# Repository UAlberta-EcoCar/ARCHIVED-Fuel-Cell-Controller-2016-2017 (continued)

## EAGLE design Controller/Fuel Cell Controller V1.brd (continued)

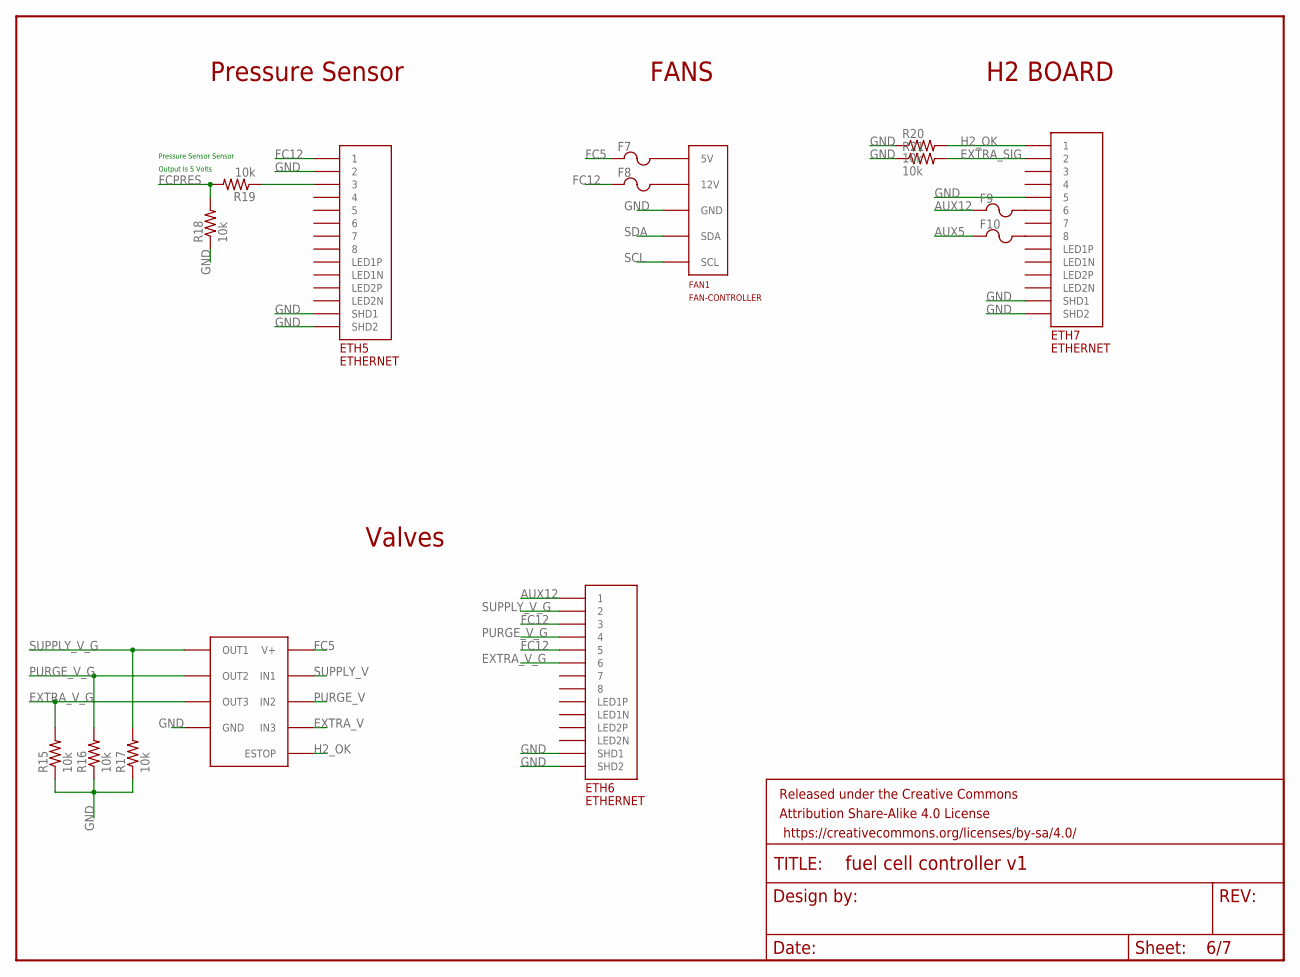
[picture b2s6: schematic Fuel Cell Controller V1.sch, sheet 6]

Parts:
ETH5, ETH6, ETH7: ETHERNET; A122645-ND
F7, F8, F9, F10: POLYFUSE; 1206
FAN1: FAN-CONTROLLER
FRAME6: FRAME-LETTERNO_PACKAGE; DUMMY
M1: MOSFETBOARD; MOSFET-BOARD
R15, R16, R17, R18, R19: 10k; 0805
R20, R21: 10k; R0603

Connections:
AUX5: F10.1; also elsewhere on the board
AUX12: ETH6.P$1 (1), F9.1; also elsewhere on the board
EXTRA_SIG: ETH7.P$2 (2), R21.2; also elsewhere on the board
EXTRA_V: M1.IN3; also elsewhere on the board
EXTRA_V_G: ETH6.P$6 (6), M1.OUT3, R15.2
FC5: F7.1, M1.VDD (V+); also elsewhere on the board
FC12: ETH5.P$1 (1), ETH6.P$3 (3), ETH6.P$5 (5), F8.1; also elsewhere on the board
FCPRES: R18.2, R19.2; also elsewhere on the board
GND: ETH5.P$2 (2), ETH5.P$13 (SHD1), ETH5.P$14 (SHD2), ETH6.P$13 (SHD1), ETH6.P$14 (SHD2), ETH7.P$5 (5), ETH7.P$13 (SHD1), ETH7.P$14 (SHD2), FAN1.GND, FAN1.GND2 (GND), FAN1.GND3 (GND), M1.GND, M1.GND1 (GND), M1.GND2 (GND), M1.VSS (GND), R15.1, R16.1, R17.1, R18.1, R20.1, R21.1; also elsewhere on the board
H2_OK: ETH7.P$1 (1), M1.ESTOP, R20.2; also elsewhere on the board
unnamed: ETH7.P$6 (6), F9.2
unnamed: ETH7.P$8 (8), F10.2
unnamed: F7.2, FAN1.5 (5V), FAN1.5_2 (5V)
unnamed: F8.2, FAN1.12 (12V), FAN1.12_2 (12V), FAN1.12_3 (12V)
unnamed: ETH5.P$3 (3), R19.1
PURGE_V: M1.IN2; also elsewhere on the board
PURGE_V_G: ETH6.P$4 (4), M1.OUT2, R16.2
SCL: FAN1.SCL; also elsewhere on the board
SDA: FAN1.SDA; also elsewhere on the board
SUPPLY_V: M1.IN1; also elsewhere on the board
SUPPLY_V_G: ETH6.P$2 (2), M1.OUT1, R17.2

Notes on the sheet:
Valves
Pressure Sensor
FANS
H2 BOARD
Pressure Sensor Sensor
Output Is 5 Volts

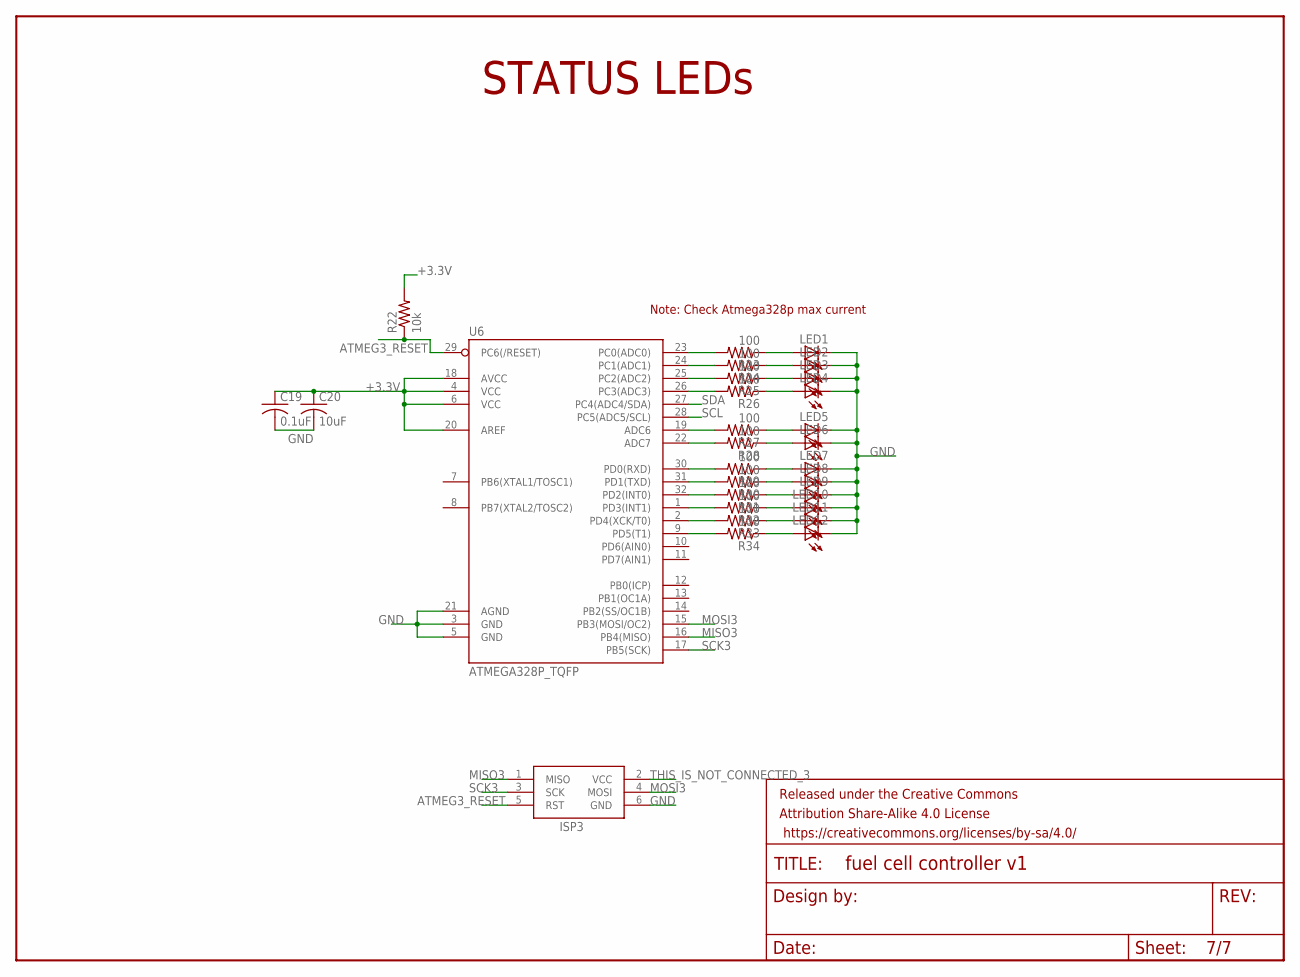
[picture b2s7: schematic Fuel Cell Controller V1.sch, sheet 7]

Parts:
C19: 0.1uF; C0603
C20: 10uF; C0603
FRAME7: FRAME-LETTERNO_PACKAGE; DUMMY
ISP3: AVRISP-BOX
LED1, LED2, LED3, LED4, LED5, LED6, LED7, LED8, LED9, LED10, LED11, LED12: LEDCHIPLED_0805; CHIPLED_0805
R22: 10k; R0603
R23, R24, R25, R26, R27, R28, R29, R30, R31, R32, R33, R34: 100; R0603
U6: ATMEGA328P_TQFP; TQFP32-08

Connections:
+3.3V: C19.1, C20.1, R22.2, U6.4 (VCC), U6.6 (VCC), U6.18 (AVCC), U6.20 (AREF); also elsewhere on the board
ATMEG3_RESET: ISP3.5 (RST), R22.1, U6.29 (PC6(/RESET))
GND: C19.2, C20.2, ISP3.6 (GND), LED1.C, LED2.C, LED3.C, LED4.C, LED5.C, LED6.C, LED7.C, LED8.C, LED9.C, LED10.C, LED11.C, LED12.C, U6.3 (GND), U6.5 (GND), U6.21 (AGND); also elsewhere on the board
MISO3: ISP3.1 (MISO), U6.16 (PB4(MISO))
MOSI3: ISP3.4 (MOSI), U6.15 (PB3(MOSI/OC2))
unnamed: R23.2, U6.23 (PC0(ADC0))
unnamed: R24.2, U6.24 (PC1(ADC1))
unnamed: R25.2, U6.25 (PC2(ADC2))
unnamed: R26.2, U6.26 (PC3(ADC3))
unnamed: R27.2, U6.19 (ADC6)
unnamed: R28.2, U6.22 (ADC7)
unnamed: R29.2, U6.30 (PD0(RXD))
unnamed: R30.2, U6.31 (PD1(TXD))
unnamed: R31.2, U6.32 (PD2(INT0))
unnamed: R32.2, U6.1 (PD3(INT1))
unnamed: R33.2, U6.2 (PD4(XCK/T0))
unnamed: R34.2, U6.9 (PD5(T1))
unnamed: LED12.A, R34.1
unnamed: LED11.A, R33.1
unnamed: LED10.A, R32.1
unnamed: LED9.A, R31.1
unnamed: LED8.A, R30.1
unnamed: LED7.A, R29.1
unnamed: LED6.A, R28.1
unnamed: LED5.A, R27.1
unnamed: LED4.A, R26.1
unnamed: LED3.A, R25.1
unnamed: LED2.A, R24.1
unnamed: LED1.A, R23.1
SCK3: ISP3.3 (SCK), U6.17 (PB5(SCK))
SCL: U6.28 (PC5(ADC5/SCL)); also elsewhere on the board
SDA: U6.27 (PC4(ADC4/SDA)); also elsewhere on the board
THIS_IS_NOT_CONNECTED_3: ISP3.2 (VCC)

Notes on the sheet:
STATUS LEDs
Note: Check Atmega328p max current

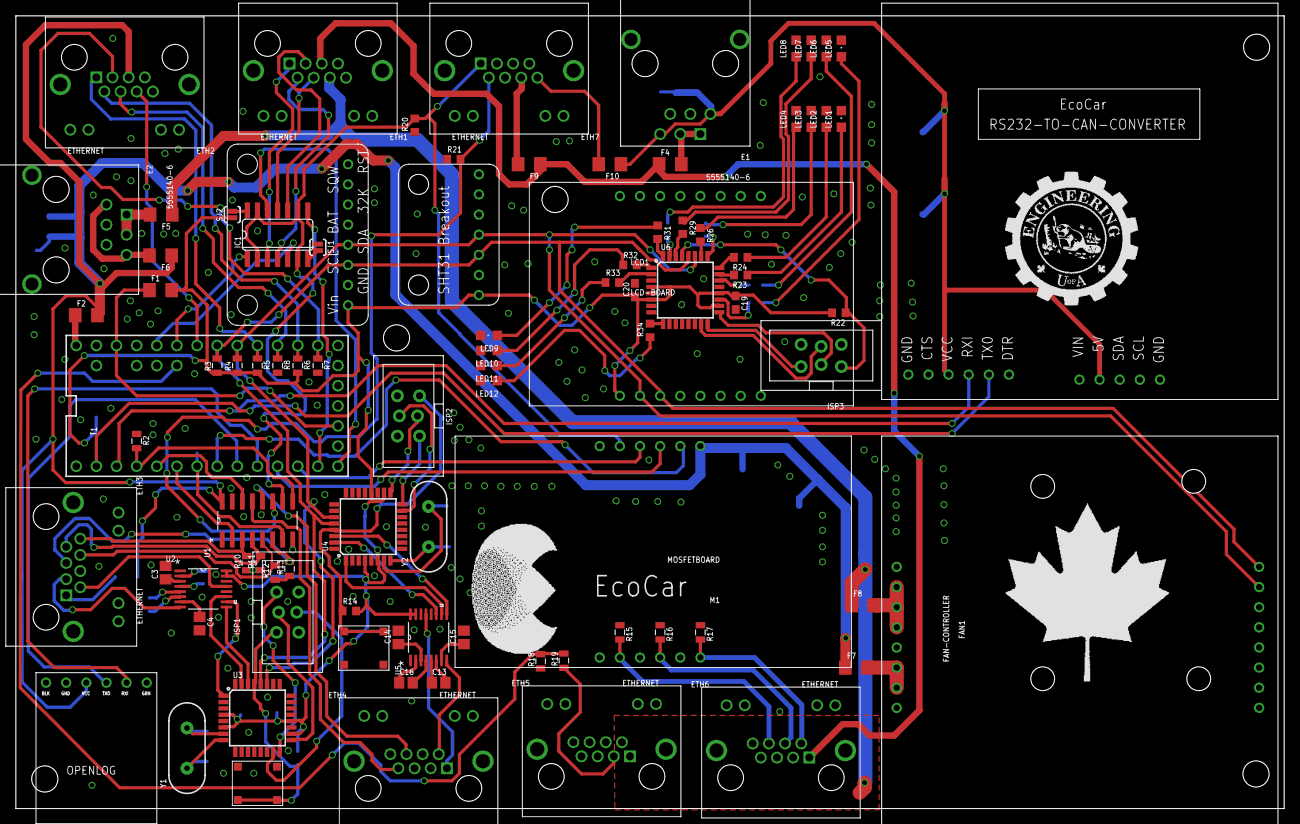
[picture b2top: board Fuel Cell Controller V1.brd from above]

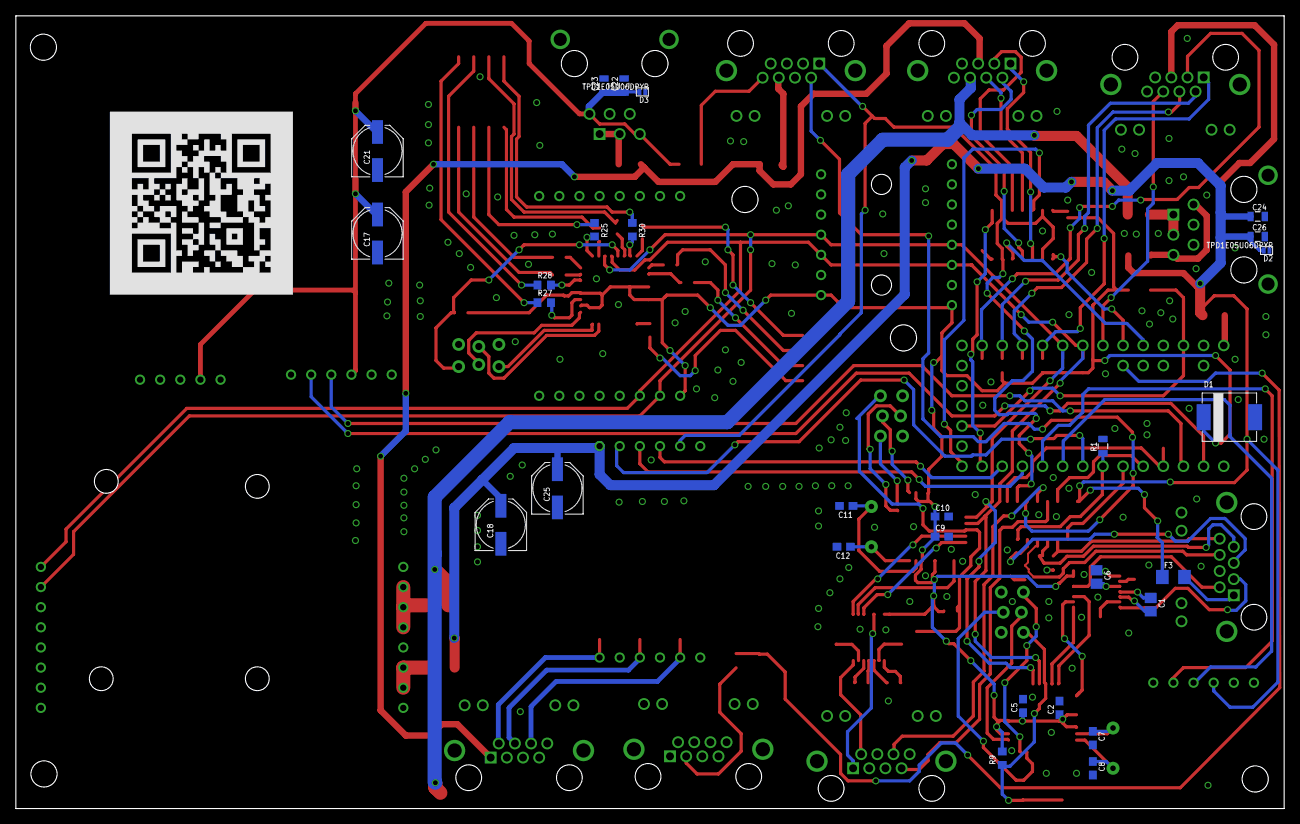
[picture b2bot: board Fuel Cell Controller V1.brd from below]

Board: 2 copper layers, 160.0 x 100.0 mm, 131 parts (29 on the bottom side), 119 nets.

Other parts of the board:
U$1: TRUMP

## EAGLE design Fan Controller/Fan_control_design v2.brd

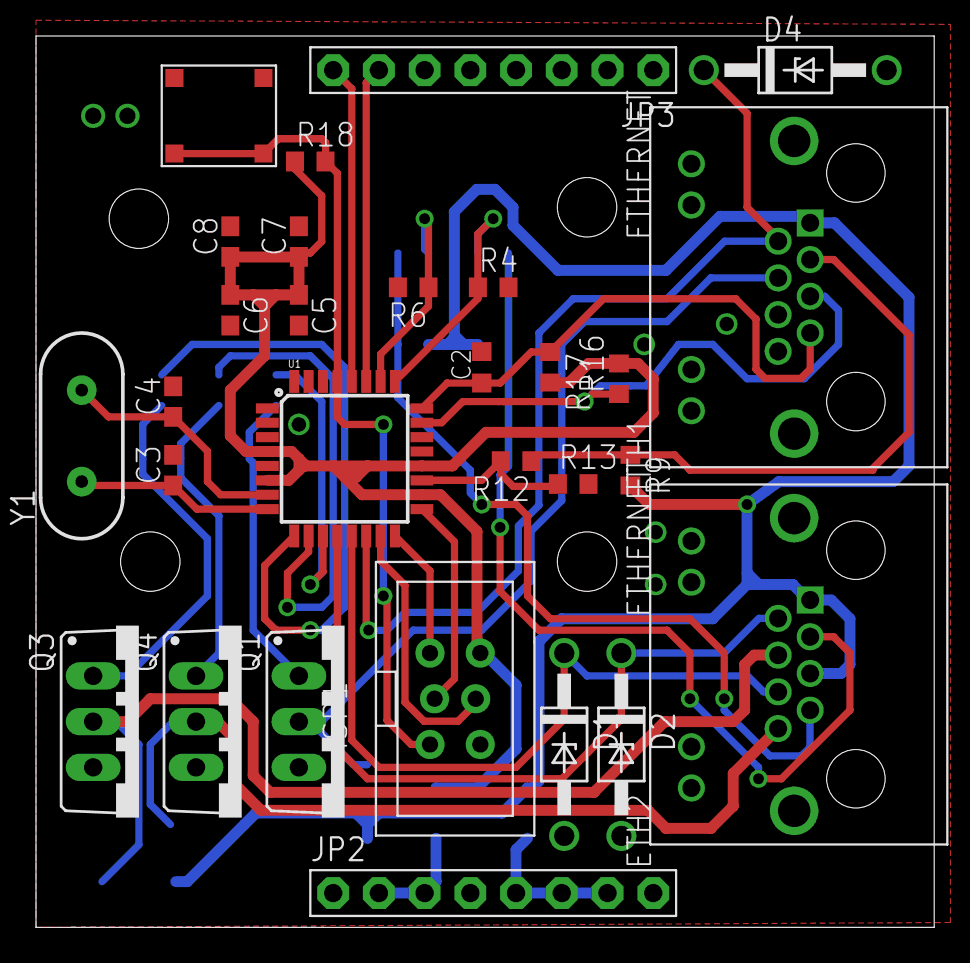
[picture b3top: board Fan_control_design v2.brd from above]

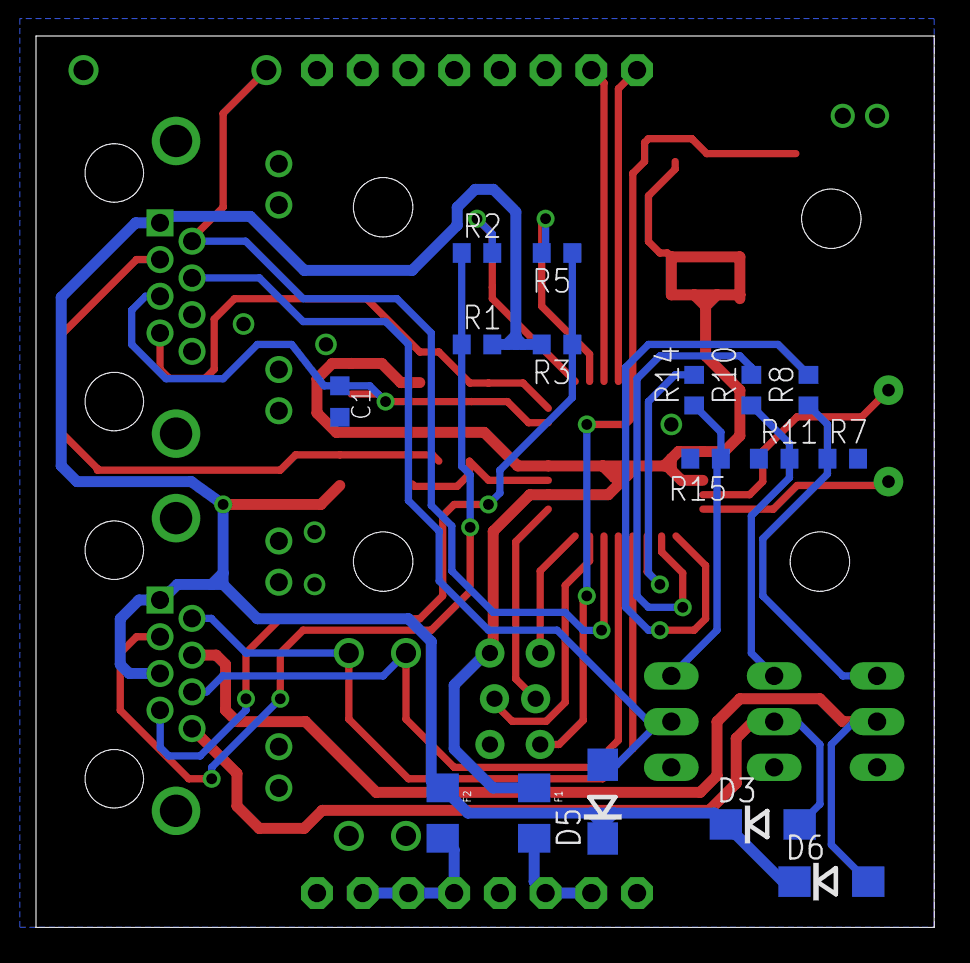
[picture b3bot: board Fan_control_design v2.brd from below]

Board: 2 copper layers, 49.9 x 49.5 mm, 49 parts (16 on the bottom side), 33 nets.

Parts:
C1, C2: C0603K
C3, C4: 22pf; C0603
C5, C6: 0.1uf; C0603
C7, C8: 10uf; C0603
D1, D2, D4: 1N4728; DO41Z10
D3, D5, D6: DO214AC
ETH1, ETH2: ETHERNET; A122645-ND
F1, F2: 1206
ISP1: AVRISP-BOX
JP2, JP3: 1X08-BIG
Q1, Q3, Q4: IRF520; TO220BV
R1, R2, R3, R5, R7, R9, R11, R12, R15, R18: 10k; R0603
R4, R6, R13: 4k7; R0603
R8, R10, R14: 250; R0603
R16, R17: 100K; R0603
STANDOFF1, STANDOFF2, STANDOFF3, STANDOFF4: STAND-OFF
U1: ATMEGA328P_TQFP; TQFP32-08
U$3: EG4621CT-ND
Y1: HC49US

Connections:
12V: D3.C, D5.C, D6.C, ETH1.P$1, ETH2.P$1, ETH2.P$5, F2.1, R1.2, R3.2, R9.2
+5V: C5.1, C6.1, C7.1, C8.1, F1.1, ISP1.2, R16.2, R17.2, R18.1, U1.4, U1.6, U1.18, U1.20
GND: C1.2, C2.2, C3.2, C4.2, C5.2, C6.2, C7.2, C8.2, D1.A, D2.A, D4.A, ETH1.P$6, ETH1.P$8, ETH1.P$13, ETH1.P$14, ETH2.P$13, ETH2.P$14, ISP1.6, JP3.4, JP3.5, JP3.6, Q1.S, Q3.S, Q4.S, R4.2, R6.2, R7.2, R11.1, R13.2, R15.1, U1.3, U1.5, U1.21, U$3.P$1, U$3.P$2
MISO: ISP1.1, U1.16
MOSI: ISP1.4, U1.15
MOS_1: R8.2, U1.9
MOS_2: R10.2, U1.10
MOS_3: R14.2, U1.11
unnamed: F1.2, JP2.2, JP2.3
unnamed: F2.2, JP2.5, JP2.6, JP2.7
unnamed: C3.1, U1.8, Y1.1
unnamed: Q3.G, R7.1, R8.1
unnamed: C4.1, U1.7, Y1.2
unnamed: Q4.G, R10.1, R11.2
unnamed: Q1.G, R14.1, R15.2
PWM_1: D2.C, ETH2.P$2, U1.12
PWM_2: D1.C, ETH2.P$6, U1.13
PWM_3: D4.C, ETH1.P$2, U1.14
PWR_1: D6.A, ETH2.P$4, Q3.D
PWR_2: D3.A, ETH2.P$8, Q4.D
PWR_3: D5.A, ETH1.P$4, Q1.D
RESET: ISP1.5, R18.2, U1.29, U$3.P$3, U$3.P$4
SCK: ISP1.3, U1.17
SCL: JP3.8, U1.28
SDA: JP3.7, U1.27
TACH_1: R2.2, R4.1, U1.25
TACH_1_IN: ETH2.P$3, R1.1, R2.1
TACH_2: R5.2, R6.1, U1.26
TACH_2_IN: ETH2.P$7, R3.1, R5.1
TACH_3: R12.2, R13.1, U1.19
TACH_3_IN: ETH1.P$3, R9.1, R12.1
THERM1: C1.1, ETH1.P$5, R16.1, U1.23
THERM2: C2.1, ETH1.P$7, R17.1, U1.24

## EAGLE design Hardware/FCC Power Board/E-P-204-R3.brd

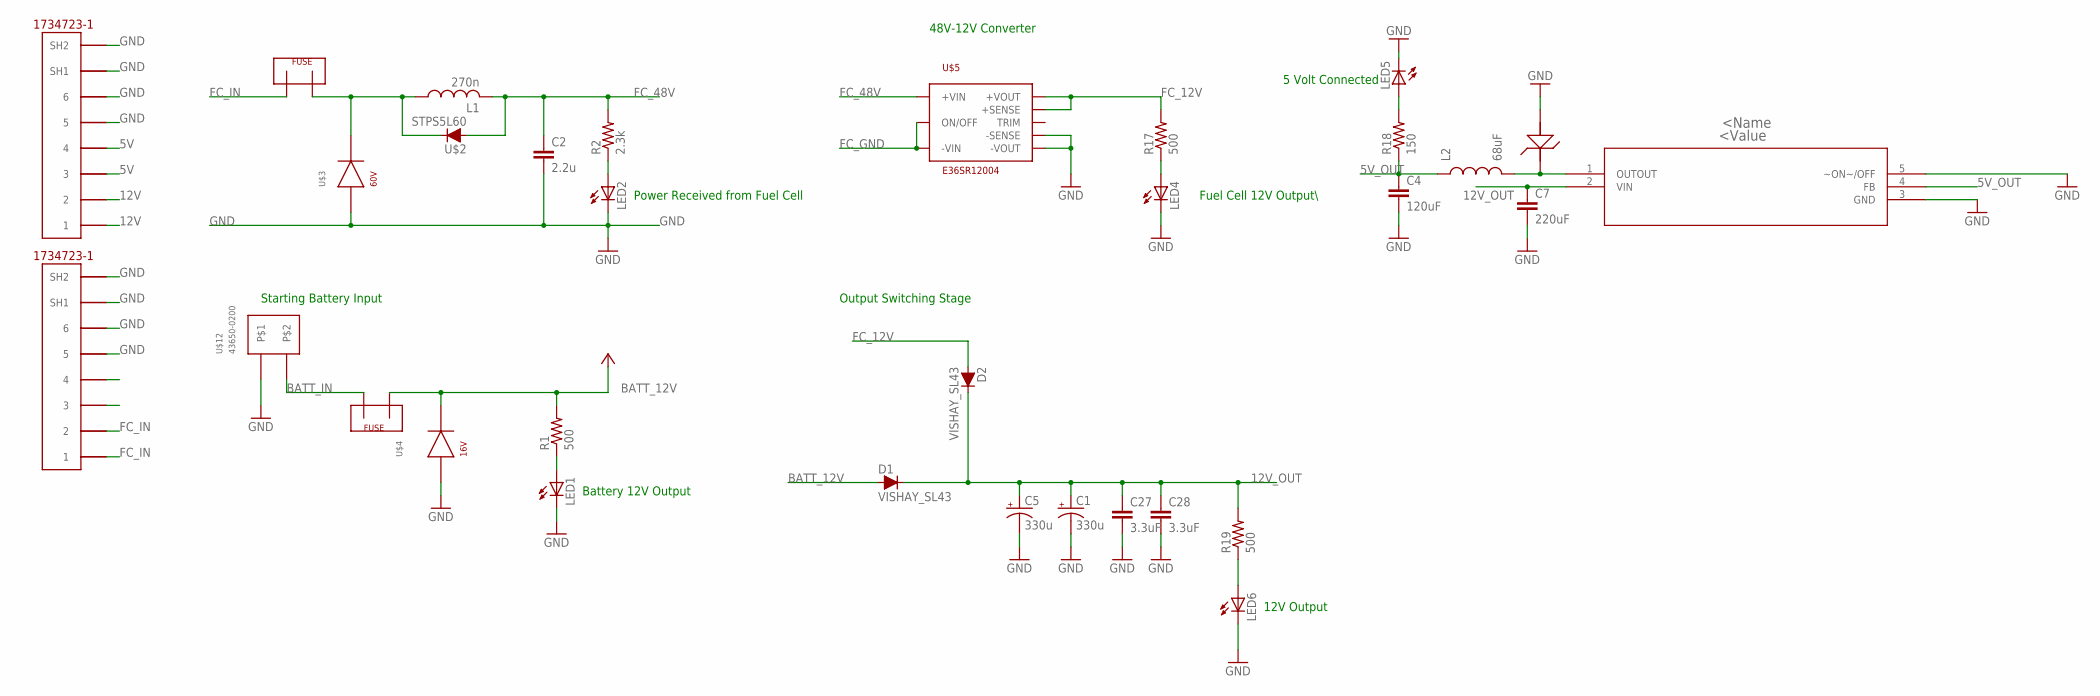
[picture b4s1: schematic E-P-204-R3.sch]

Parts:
C1, C5: 330u; PANASONIC_E
C2: 2.2u; C1210
C4: 120uF; 0805
C7: 220uF; 0805
C27, C28: 3.3uF; C0805K
D1, D2: VISHAY_SL43; DO-214AB_SMC
L1: 270n; L3225P
L2: 68uF; 0805
LED1, LED2, LED4, LED5, LED6: LED1206; LED-1206
R1, R17, R19: 500; M0805
R2: 2.3k; M0805
R18: 150; M0805
U$2: STPS5L60; STM_SMC
U$3: SMBJ60CA; .277X.089
U$4: SMAJ16CA; .25X.07
U$5: E36SR12004; 2.30X0.90X0.34
U$6, U$11: 5555140-6; 1734723-1_RJ11
U$7, U$10: FUSEMINI-BLADE; MINI-BLADE-FUSE
U$8: LM2595T-5.0; T05D
U$9: MURS120T3G
U$12: 43650-0200

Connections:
5V: U$11.3, U$11.4
5V_OUT: C4.1, L2.1, R18.1, U$8.4 (FB)
12V: U$11.1, U$11.2
12V_OUT: C1.+, C5.+, C7.1, C27.1, C28.1, D1.C, D2.C, R19.2, U$8.2 (VIN)
BATT_12V: D1.A, R1.2, U$4.CATHODE, U$10.OUT
BATT_IN: U$10.IN, U$12.P$1
FC_12V: D2.A, R17.2, U$5.P$7 (+SENSE), U$5.P$8 (+VOUT)
FC_48V: C2.1, L1.2, R2.2, U$2.A, U$5.P$1 (+VIN)
FC_FUSED: L1.1, U$2.C, U$3.CATHODE, U$7.IN
FC_GND: U$5.P$2 (ON/OFF), U$5.P$3 (-VIN)
FC_IN: U$6.1, U$6.2, U$7.OUT
GND: C1.-, C2.2, C4.2, C5.-, C7.2, C27.2, C28.2, LED1.C, LED2.C, LED4.C, LED5.C, LED6.C, U$3.ANODE, U$4.ANODE, U$5.P$4 (-VOUT), U$5.P$5 (-SENSE), U$6.5, U$6.6, U$6.SH1, U$6.SH2, U$8.3 (GND), U$8.5 (~ON~/OFF), U$9.P$2 (PIN1), U$11.5, U$11.6, U$11.SH1, U$11.SH2, U$12.P$2
unnamed: LED1.A, R1.1
unnamed: LED2.A, R2.1
unnamed: L2.2, U$8.1 (OUTOUT), U$9.P$1
unnamed: LED5.A, R18.2
unnamed: LED4.A, R17.1
unnamed: LED6.A, R19.1

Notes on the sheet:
Output Switching Stage
Starting Battery Input
48V-12V Converter
Power Received from Fuel Cell
Battery 12V Output
Fuel Cell 12V Output\
12V Output
5 Volt Connected

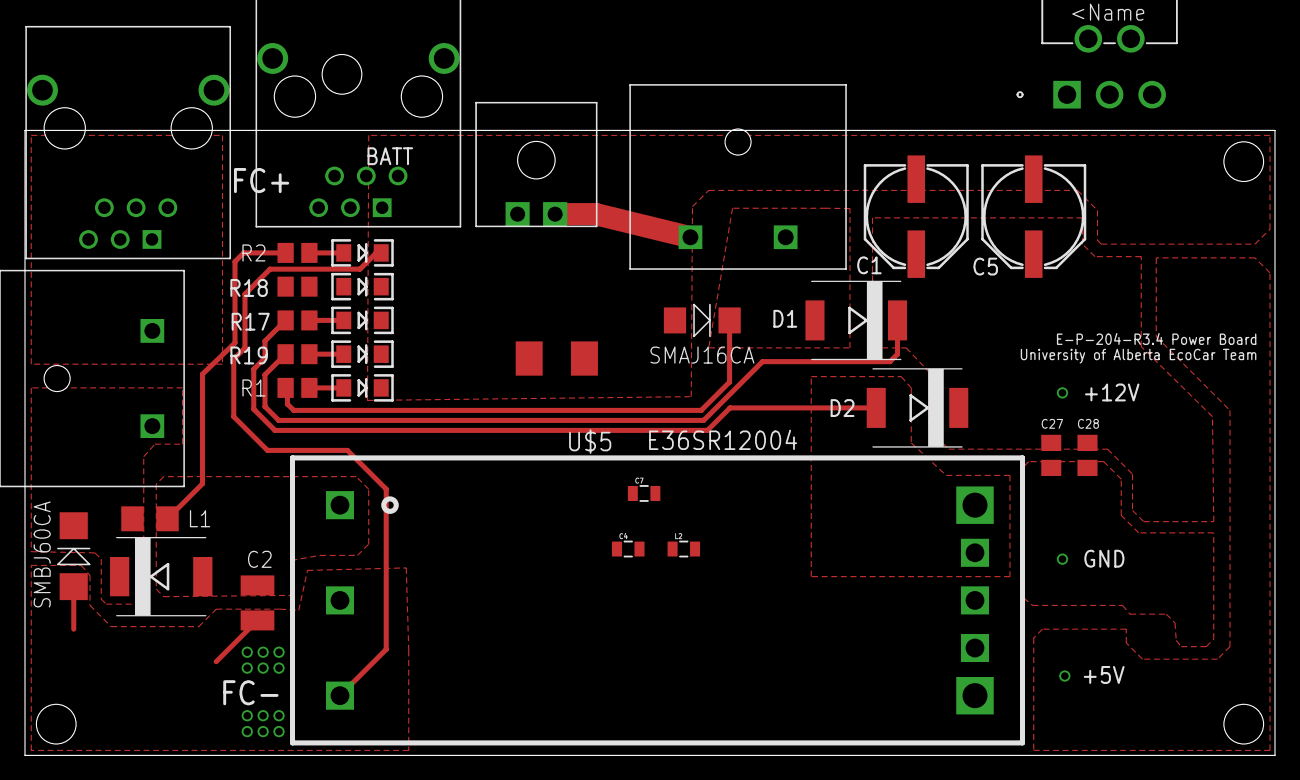
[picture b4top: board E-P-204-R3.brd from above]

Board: 2 copper layers, 100.0 x 50.0 mm, 32 parts (0 on the bottom side), 18 nets.

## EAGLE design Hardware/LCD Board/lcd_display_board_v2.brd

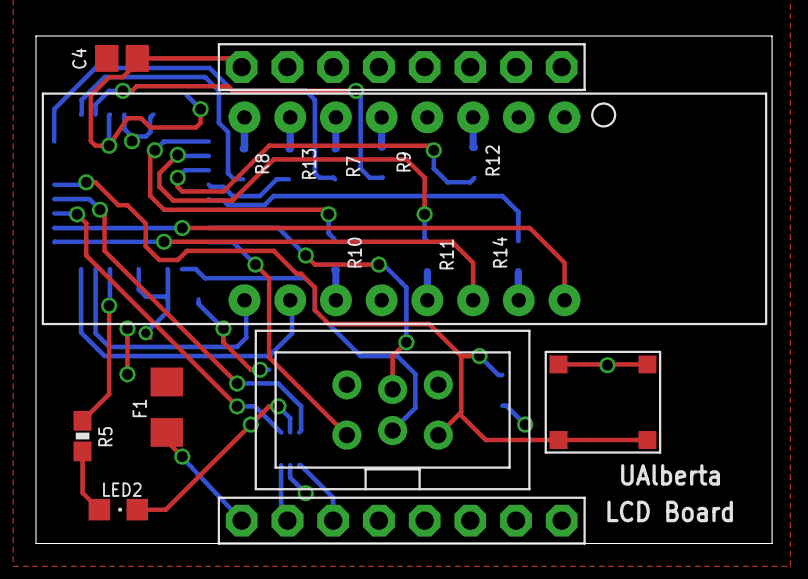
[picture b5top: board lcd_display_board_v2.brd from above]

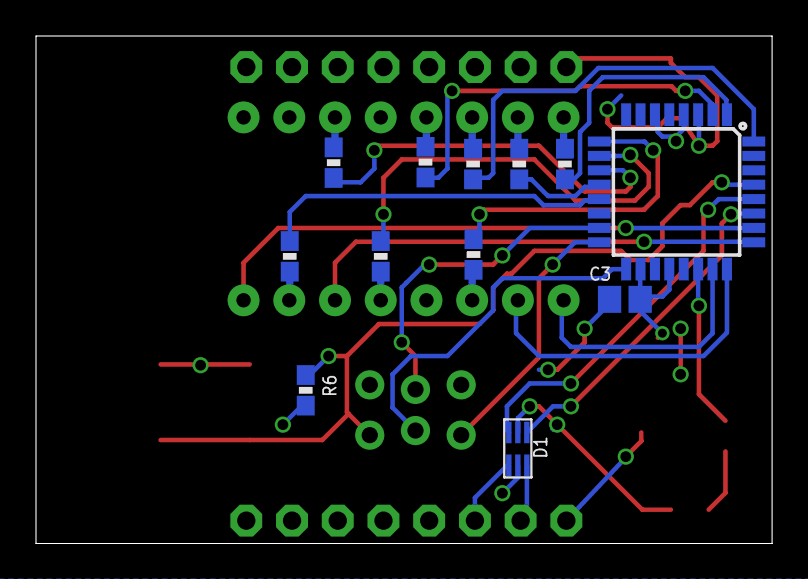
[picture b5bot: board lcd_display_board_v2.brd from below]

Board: 2 copper layers, 40.9 x 28.2 mm, 21 parts (12 on the bottom side), 33 nets.

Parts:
C3: 1uF; C0805
C4: 0.1uF; C0805
D1: USBLC6-2SC6
F1: 1206
ISP1: AVRISP-BOX
JP1, JP2: 1X08-BIG
LED1: 7-SEGMENT-4DIGIT-YOUNGSUN
LED2: CHIPLED_0805
R5: 1k; 0603-RES
R6: 10k; 0603-RES
R7, R8, R9, R10, R11, R12, R13, R14: 80 Ohm; 0603-RES
U1: ATMEGA328P_TQFP; TQFP32-08
U$10: EG4621CT-ND

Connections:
+3.3V: C3.1, C4.1, D1.P$5, F1.1, R6.2, U1.4, U1.6, U1.18, U1.20
ATM_RESET: ISP1.5, R6.1, U1.29, U$10.P$3, U$10.P$4
DIG1AN: LED1.1, U1.23
DIG2AN: LED1.2, U1.24
DIG3AN: LED1.6, U1.25
DIG4AN: LED1.8, U1.26
GND: C3.2, C4.2, D1.P$2, ISP1.6, JP1.4, JP1.5, JP1.6, JP1.7, JP1.8, JP2.1, JP2.2, JP2.3, JP2.4, JP2.5, JP2.6, JP2.7, JP2.8, LED2.C, U1.3, U1.5, U1.21, U$10.P$1, U$10.P$2
MISO: ISP1.1, U1.16
MOSI: ISP1.4, U1.15
unnamed: F1.2, JP1.1
unnamed: D1.P$6, JP1.2
unnamed: R5.1, U1.22
unnamed: LED2.A, R5.2
unnamed: R7.1, U1.32
unnamed: R8.1, U1.1
unnamed: R9.1, U1.2
unnamed: R10.1, U1.9
unnamed: R11.1, U1.10
unnamed: R12.1, U1.11
unnamed: R13.1, U1.12
unnamed: R14.1, U1.13
unnamed: D1.P$4, JP1.3
SCK: ISP1.3, U1.17
SCL: D1.P$3, U1.28
SDA: D1.P$1, U1.27
SEGA: LED1.14, R7.2
SEGB: LED1.16, R8.2
SEGC: LED1.13, R9.2
SEGD: LED1.3, R10.2
SEGDP: LED1.7, R14.2
SEGE: LED1.5, R11.2
SEGF: LED1.11, R12.2
SEGG: LED1.15, R13.2

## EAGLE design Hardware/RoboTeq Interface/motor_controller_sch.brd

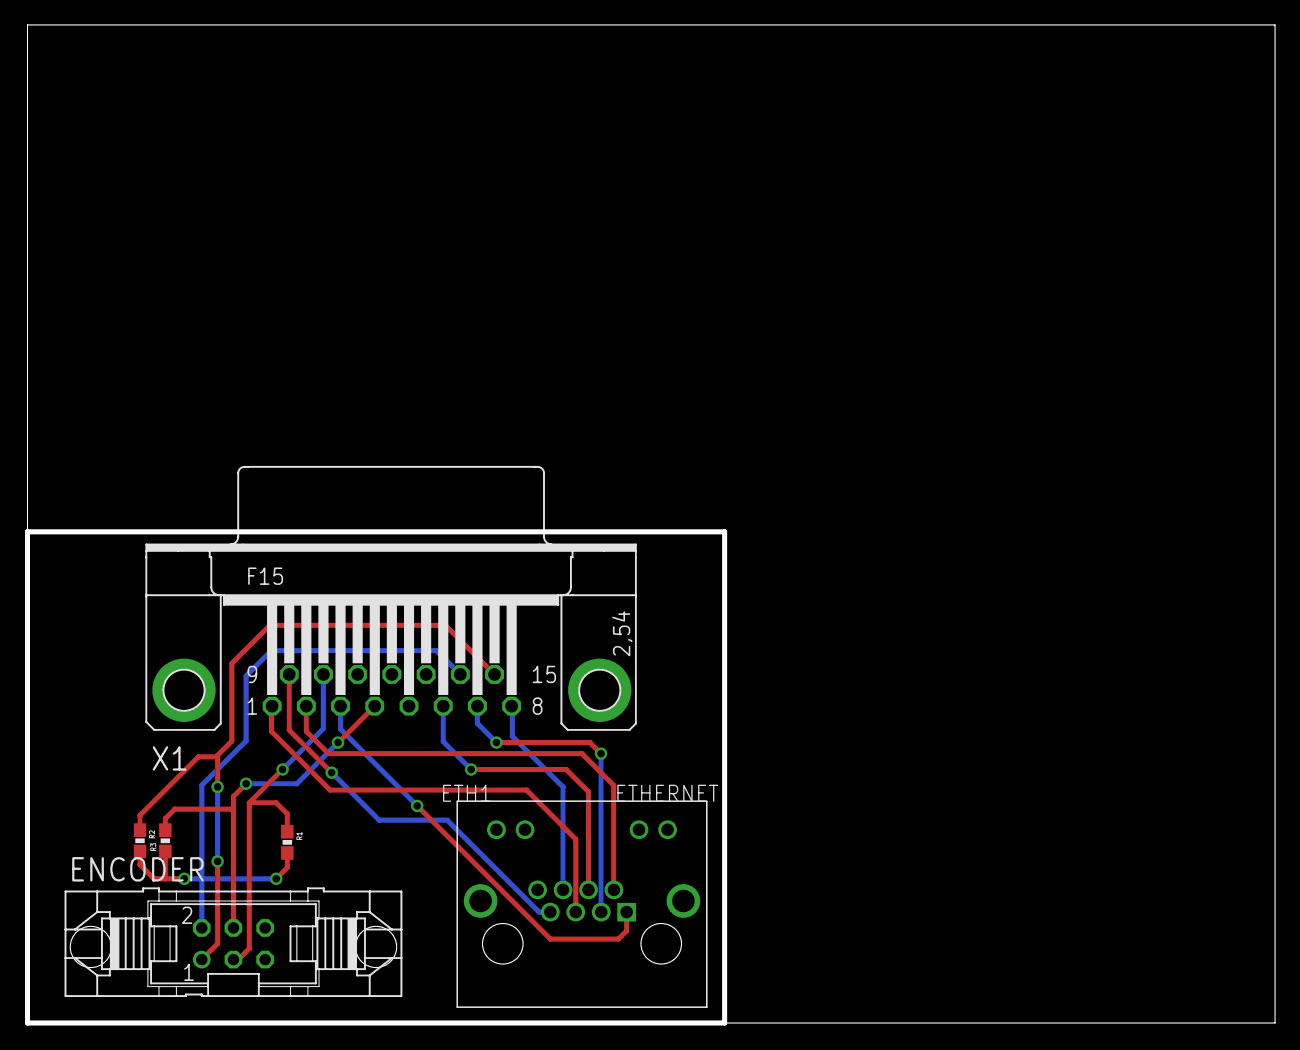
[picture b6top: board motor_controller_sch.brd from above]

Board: 2 copper layers, 100.0 x 80.0 mm, 6 parts (0 on the bottom side), 12 nets.

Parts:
ENCODER: 06V
ETH1: ETHERNET; A122645-ND
R1, R2, R3: 3.3k; 0603-RES
X1: F15HP

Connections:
5V: ENCODER.2, R1.2, R2.2, R3.1, X1.14
CANH: ETH1.P$4, X1.6
CANL: ETH1.P$3, X1.7
DI1: ETH1.P$6, X1.8
DI2: ETH1.P$7, X1.9
DO1: ETH1.P$5, X1.1
ENCA: ENCODER.3, R1.1, X1.10
ENCB: ENCODER.1, R2.1, X1.15
GND: ENCODER.5, ENCODER.6, X1.5, X1.13
INDEX: ENCODER.4, R3.2, X1.4
RX: ETH1.P$1, X1.3
TX: ETH1.P$2, X1.2
